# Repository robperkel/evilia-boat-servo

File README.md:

# Dr. Evilia's Boat Sampling HAT
This custom HAT is used to better implement control of the servos and motors used on her sampling boat. We found there wasn't a good "off-the-shelf" board available that fit the desired specifications. This project is designed around a small, 8-bit microcontroller that provides a far more intelligent and flexible design interface. 

This repository contains the documentation, hardware files, and firmware used for this project. The boat runs on a Raspberry Pi 4, Model B.  

## Table of Contents

- [Base Software](#base-software)
- [Tools Needed](#tools-needed)
    - [Other Tools Used](#other-tools-used)
- [Bill of Materials (BOM)](#bill-of-materials-bom)
- [Design Objectives](#design-objectives)
- [Microcontroller Pinout](#microcontroller-pinout)
- [Software Registers](#software-registers)
- [Digital Control](#digital-control)
- [Analog Control](#analog-control)
- [Usage from Raspberry Pi](#usage-from-raspberry-pi)

## Base Software

This bare metal I<sup>2</sup>C driver was used as a code base: https://github.com/microchip-pic-avr-examples/pic18f56q71-bare-metal-i2c-mplab 

**Per the license agreement in this code, the firmware (specifically the I<sup>2</sup>C driver) can ONLY be used with Microchip microcontrollers.** This is not an issue as the physical board is not compatiable with other microcontrollers.

## Tools Needed

- Programming / Development IDE: [MPLAB&reg; X IDE v6.10](https://www.microchip.com/en-us/tools-resources/develop/mplab-x-ide)
- Compiler: [MPLAB XC8 v2.41](https://www.microchip.com/en-us/tools-resources/develop/mplab-xc-compilers/downloads-documentation#XC8)  
- Programmer: [MPLAB SNAP](https://www.microchip.com/en-us/development-tool/PG164100) or [PICKIT&trade; 4](https://www.microchip.com/en-us/development-tool/PG164140)

### Other Tools Used

- I<sup>2</sup>C Tester (for development): [MCP2221A Breakout Module (ADM00559)](https://www.microchip.com/en-us/development-tool/ADM00559)
- Block Diagrams: [Draw.io](https://app.diagrams.net/)
- Schematic and PCB Generation: [KiCad 7](https://www.kicad.org/)
- PCB Vendor: [OSH Park](https://oshpark.com/)
    - If ordering from a different vendor, I recommend choosing a surface finish such as ENIG to provide some corrosion resistance in the high humidity environment.
    - Conformally coating the board is also recommended.

## Bill of Materials (BOM)

Order PCBs directly from the [OSH Park Project Page](https://oshpark.com/shared_projects/IClJSFr6)  
Digikey Shopping List: [https://www.digikey.com/en/mylists/list/YOLHZE0EBO](https://www.digikey.com/en/mylists/list/YOLHZE0EBO)   
- See [Control Board.xlsx](./Control%20Board/Control%20Board.xlsx) for the BOM
    - Red, struck-through items are not in the BOM
- Includes 0 ohm jumpers for I<sup>2</sup>C Address Setting
- Motor drive parts for `EXT_LED1` are not included
- Optional off-board connectors are not in the list

**Important: Shopping list does NOT include a programmer. Programmers can obtained from Digikey (or other electronics vendor).**

## Design Objectives

1. Support 6x 3-pin servo motors
2. ON/OFF control of a large pump
3. LED outputs for various indicators
4. I<sup>2</sup>C Interface
5. 3.3V logic interface with Raspberry Pi
6. 5V, 500mA motor control (ON/OFF)
7. 50 Hz Servo Frequency

## Microcontroller Pinout

Microcontroller: PIC18F1xQ41
(PIC18F14Q41 / PIC18F15Q41 / PIC18F16Q41)

| Function | Pin (PORT / PIN)
| -------- | ----------
| VDD (5V) | 1
| VSS (GND) | 20
| nMCLR | 4
| SDA | 2 (RA5)
| SCL | 3 (RA4)
| ADDR0 | 16 (RC0)
| ADDR1 | 13 (RB4)
| Servo 6 | 10 (RB7)
| Servo 5 | 9 (RC7)
| Servo 4 | 8 (RC6)
| Servo 3 | 7 (RC3)
| Servo 2 | 6 (RC4)
| Servo 1 | 5 (RC5)
| EXT_LED | 11 (RB6)
| PUMP_EN | 15 (RC1)
| AN1 | 17 (RA2)
| AN2 | 12 (RB5)
| DEBUG 0 | 19 (RA0 / ICSPDAT)
| DEBUG 1 | 18 (RA1 / ICSPCLK)
| OPAMP_OUT (reserved) | 14 (RC2)

### Notes
1. nMCLR is not available as an I/O in this configuration.
2. DEBUG 0/1 are LED outputs on the board. Unavailable during debugging.
3. EXT_LED can be converted to a 2nd motor/pump enable.
4. OPAMP_OUT is reserved due to internal OPAMP peripheral requirements.  

## Software Registers

**Please see [Registers.md](./Registers.md) for more information**

## Digital Control

### I<sup>2</sup>C Parameters

- Frequency: 100 kHz  
- 7-bit Address: TBD

### I<sup>2</sup>C Communication

### Writing To

The "register address" (Reg. ADDR) selects which setting to change. After this, each data byte is loaded into the next sequential register. 

(Start) &rarr; I<sup>2</sup>C ADDR (W) &rarr; Reg. ADDR &rarr; Data 0 &rarr; Data 1 &rarr; ... &rarr; Data N &rarr; (Stop)

### Reading From

To read from the device, address the microcontroller (write) and send the starting register address. Then, restart communication and address the microcontroller (read). Each byte is read in order from the registers.

(Start) &rarr; I<sup>2</sup>C ADDR (W) &rarr; Reg. ADDR &rarr; (Restart) &rarr; I<sup>2</sup>C ADDR (R) &rarr; Data 0 &rarr; Data 1 &rarr; ... &rarr; Data N &rarr; (Stop)

### Power on Restart (PoR) Behavior

On PoR, the microcontroller sets all duty cycles to 0%, PWM frequencies to 50 Hz, and turns off the LEDs and motor. 

## Analog Control

## Usage from Raspberry Pi

To ease integration in the system, a custom Python library was developed to simplify setup.

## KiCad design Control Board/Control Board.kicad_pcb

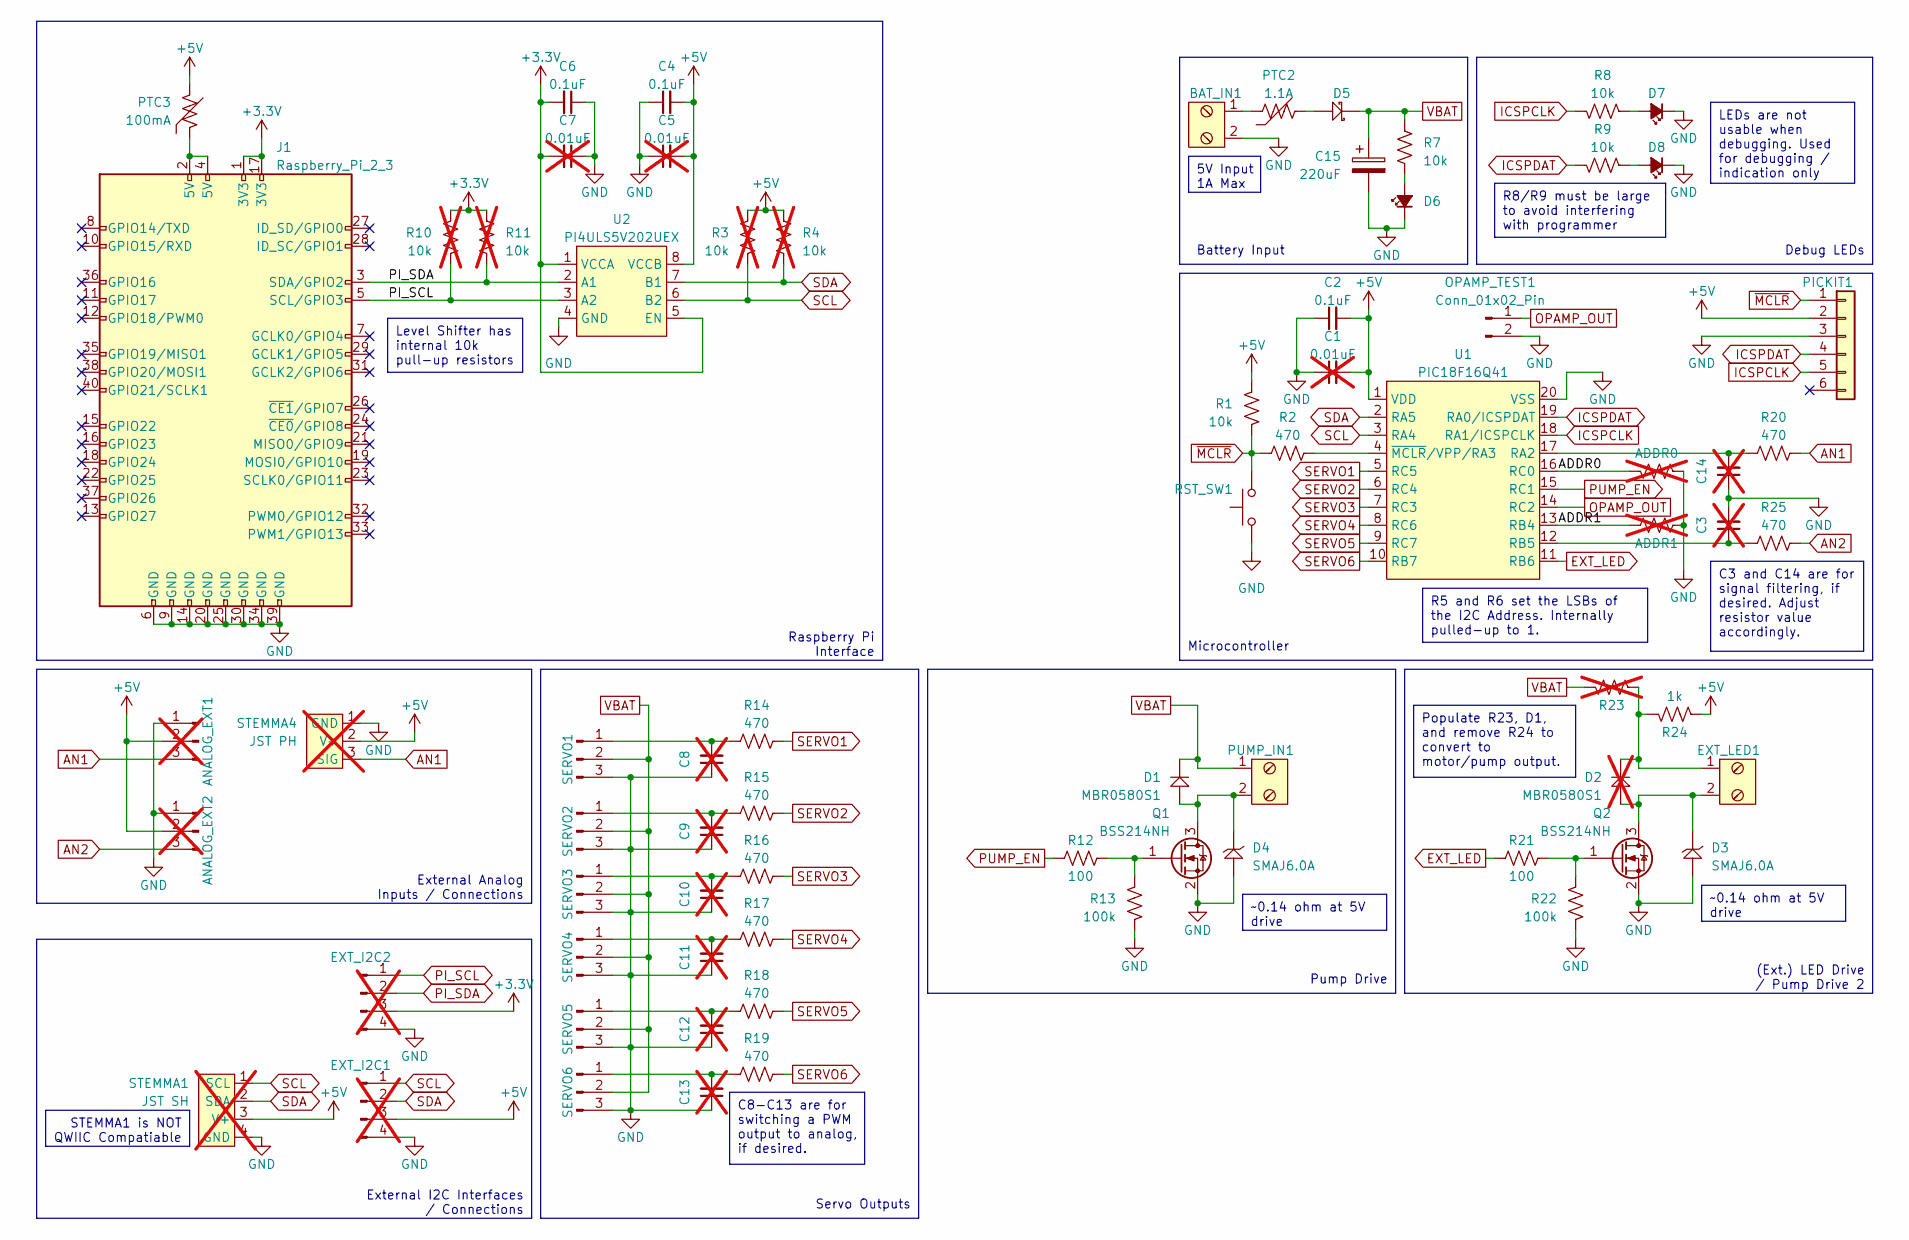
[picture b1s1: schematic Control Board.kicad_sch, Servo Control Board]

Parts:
ADDR0, ADDR1: 0; R_0805_2012Metric_Pad1.20x1.40mm_HandSolder; not fitted
ANALOG_EXT1, ANALOG_EXT2: Conn_01x03_Pin; PinHeader_1x03_P2.54mm_Vertical; not fitted
BAT_IN1: BCH-381H-2 GN; BCH-381H-2GN
C1, C3, C5, C7, C8, C9, C10, C11, C12, C13, C14: 0.01uF; C_0805_2012Metric_Pad1.18x1.45mm_HandSolder; not fitted
C2, C4, C6: 0.1uF; C_0805_2012Metric_Pad1.18x1.45mm_HandSolder
C15: 220uF; C_Radial_D8.0mm_H11.5mm_P3.50mm
D1: MBR0580S1; SOD-123
D2: MBR0580S1; SOD-123; not fitted
D3, D4: SMAJ6.0A; DO-214AC
D5: B240AE-13; DO-214AC
D6, D7, D8: LED_Small_Filled; LED_0805_2012Metric_Pad1.15x1.40mm_HandSolder
EXT_I2C1, EXT_I2C2: Conn_01x04_Pin; PinHeader_1x04_P2.54mm_Vertical; not fitted
EXT_LED1: BCH-381H-2 GN; BCH-381H-2GN
J1: Raspberry_Pi_2_3; PinHeader_2x20_P2.54mm_Vertical
OPAMP_TEST1: Conn_01x02_Pin; PinHeader_1x02_P2.54mm_Vertical
PICKIT1: Conn_01x06; PinHeader_1x06_P2.54mm_Horizontal
PTC2: 1.1A; 0ZCG Series PTC
PTC3: 100mA; 0ZCG Series PTC
PUMP_IN1: BCH-381H-2 GN; BCH-381H-2GN
Q1, Q2: BSS214NH; SOT23-3
R1, R7, R8, R9: 10k; R_0805_2012Metric_Pad1.20x1.40mm_HandSolder
R2, R14, R15, R16, R17, R18, R19, R20, R25: 470; R_0805_2012Metric_Pad1.20x1.40mm_HandSolder
R3, R4, R10, R11: 10k; R_0805_2012Metric_Pad1.20x1.40mm_HandSolder; not fitted
R12, R21: 100; R_0805_2012Metric_Pad1.20x1.40mm_HandSolder
R13, R22: 100k; R_0805_2012Metric_Pad1.20x1.40mm_HandSolder
R23: 0; R_0805_2012Metric_Pad1.20x1.40mm_HandSolder; not fitted
R24: 1k; R_0805_2012Metric_Pad1.20x1.40mm_HandSolder
RST_SW1: TL6400AF160QJ
SERVO1, SERVO2, SERVO3, SERVO4, SERVO5, SERVO6: Conn_01x03_Pin; PinHeader_1x03_P2.54mm_Vertical
STEMMA1: JST SH; Adafruit STEMMA, 4-pin JST SH; not fitted
STEMMA4: JST PH; Adafruit STEMMA, 3-pin JST PH; not fitted
U1: PIC18F16Q41; SSOP-20, 5.3mm Body
U2: PI4ULS5V202UEX; MSOP-8

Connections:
+3.3V: C6.2, C7.2, EXT_I2C2.3, J1.1 (3V3), J1.17 (3V3), R10.1, R11.1, U2.1 (VCCA), U2.5 (EN)
+5V: ANALOG_EXT1.2, ANALOG_EXT2.2, C1.2, C2.2, C4.2, C5.2, EXT_I2C1.3, PICKIT1.2, PTC3.2, R1.1, R3.1, R4.1, R24.2, STEMMA1.3 (V+), STEMMA4.2 (V+), U1.1 (VDD), U2.8 (VCCB)
/ADDR0: ADDR0.1, U1.16 (RC0)
/ADDR1: ADDR1.1, U1.13 (RB4)
AN1: ANALOG_EXT1.3, R20.2, STEMMA4.3 (SIG)
AN2: ANALOG_EXT2.3, R25.2
EXT_LED: R21.1, U1.11 (RB6)
GND: ADDR0.2, ADDR1.2, ANALOG_EXT1.1, ANALOG_EXT2.1, BAT_IN1.2, C1.1, C2.1, C3.2, C4.1, C5.1, C6.1, C7.1, C8.1, C9.1, C10.1, C11.1, C12.1, C13.1, C14.1, C15.2, D3.A, D4.A, D6.1 (K), D7.1 (K), D8.1 (K), EXT_I2C1.4, EXT_I2C2.4, J1.6 (GND), J1.9 (GND), J1.14 (GND), J1.20 (GND), J1.25 (GND), J1.30 (GND), J1.34 (GND), J1.39 (GND), OPAMP_TEST1.2, PICKIT1.3, Q1.2 (S), Q2.2 (S), R13.2, R22.2, RST_SW1.1, SERVO1.3, SERVO2.3, SERVO3.3, SERVO4.3, SERVO5.3, SERVO6.3, STEMMA1.4 (GND), STEMMA4.1 (GND), U1.20 (VSS), U2.4 (GND)
ICSPCLK: PICKIT1.5, R8.2, U1.18 (RA1/ICSPCLK)
ICSPDAT: PICKIT1.4, R9.2, U1.19 (RA0/ICSPDAT)
unnamed: BAT_IN1.1, PTC2.1
unnamed: D2.K, EXT_LED1.1, R23.2, R24.1
unnamed: D5.A, PTC2.2
unnamed: D6.2 (A), R7.2
unnamed: D7.2 (A), R8.1
unnamed: D8.2 (A), R9.1
unnamed: J1.2 (5V), J1.4 (5V), PTC3.1
unnamed: D1.A, D4.K, PUMP_IN1.2, Q1.3 (D)
unnamed: Q1.1 (G), R12.2, R13.1
unnamed: D2.A, D3.K, EXT_LED1.2, Q2.3 (D)
unnamed: Q2.1 (G), R21.2, R22.1
unnamed: C8.2, R14.1, SERVO1.1
unnamed: C9.2, R15.1, SERVO2.1
unnamed: C10.2, R16.1, SERVO3.1
unnamed: C11.2, R17.1, SERVO4.1
unnamed: C12.2, R18.1, SERVO5.1
unnamed: C13.2, R19.1, SERVO6.1
unnamed: C14.2, R20.1, U1.17 (RA2)
unnamed: C3.1, R25.1, U1.12 (RB5)
unnamed: R2.2, U1.4 (~MCLR/VPP/RA3)
OPAMP_OUT: OPAMP_TEST1.1, U1.14 (RC2)
PI_SCL: EXT_I2C2.1, J1.5 (SCL/GPIO3), R10.2, U2.3 (A2)
PI_SDA: EXT_I2C2.2, J1.3 (SDA/GPIO2), R11.2, U2.2 (A1)
PUMP_EN: R12.1, U1.15 (RC1)
SCL: EXT_I2C1.1, R3.2, STEMMA1.1 (SCL), U1.3 (RA4), U2.6 (B2)
SDA: EXT_I2C1.2, R4.2, STEMMA1.2 (SDA), U1.2 (RA5), U2.7 (B1)
SERVO1: R14.2, U1.5 (RC5)
SERVO2: R15.2, U1.6 (RC4)
SERVO3: R16.2, U1.7 (RC3)
SERVO4: R17.2, U1.8 (RC6)
SERVO5: R18.2, U1.9 (RC7)
SERVO6: R19.2, U1.10 (RB7)
VBAT: C15.1, D1.K, D5.K, PUMP_IN1.1, R7.1, R23.1, SERVO1.2, SERVO2.2, SERVO3.2, SERVO4.2, SERVO5.2, SERVO6.2
~MCLR: PICKIT1.1, R1.2, R2.1, RST_SW1.2

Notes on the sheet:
Populate R23, D1, and remove R24 to convert to motor/pump output.
Debug LEDs
External Analog Inputs / Connections
Battery Input
~0.14 ohm at 5V drive
R8/R9 must be large to avoid interfering with programmer
5V Input 1A Max
C3 and C14 are for signal filtering, if desired. Adjust resistor value accordingly.
C8-C13 are for switching a PWM output to analog, if desired.
External I2C Interfaces / Connections
LEDs are not usable when debugging. Used for debugging / indication only
Pump Drive
Level Shifter has internal 10k pull-up resistors
R5 and R6 set the LSBs of the I2C Address. Internally pulled-up to 1.
Servo Outputs
Microcontroller
(Ext.) LED Drive / Pump Drive 2
STEMMA1 is NOT QWIIC Compatiable
Raspberry Pi Interface

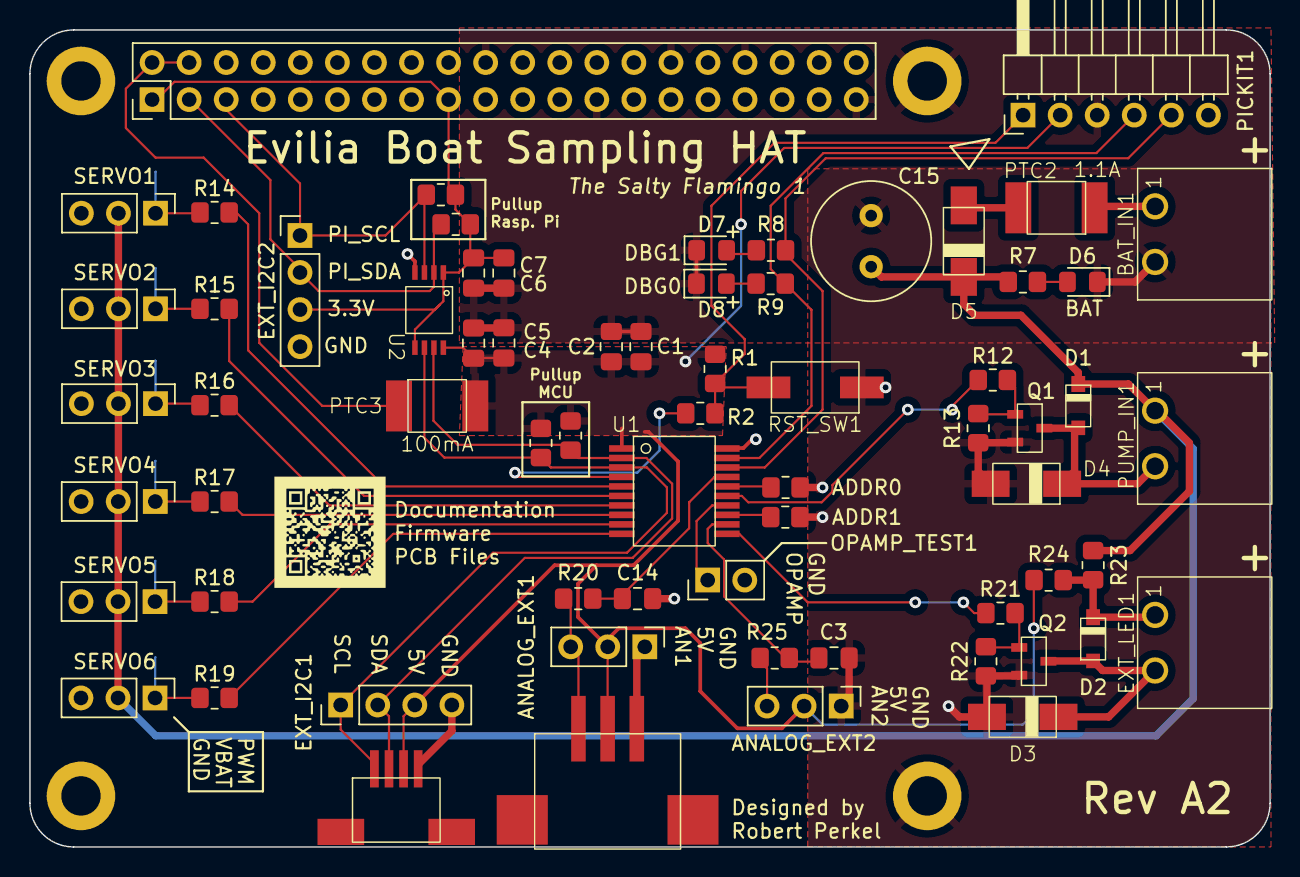
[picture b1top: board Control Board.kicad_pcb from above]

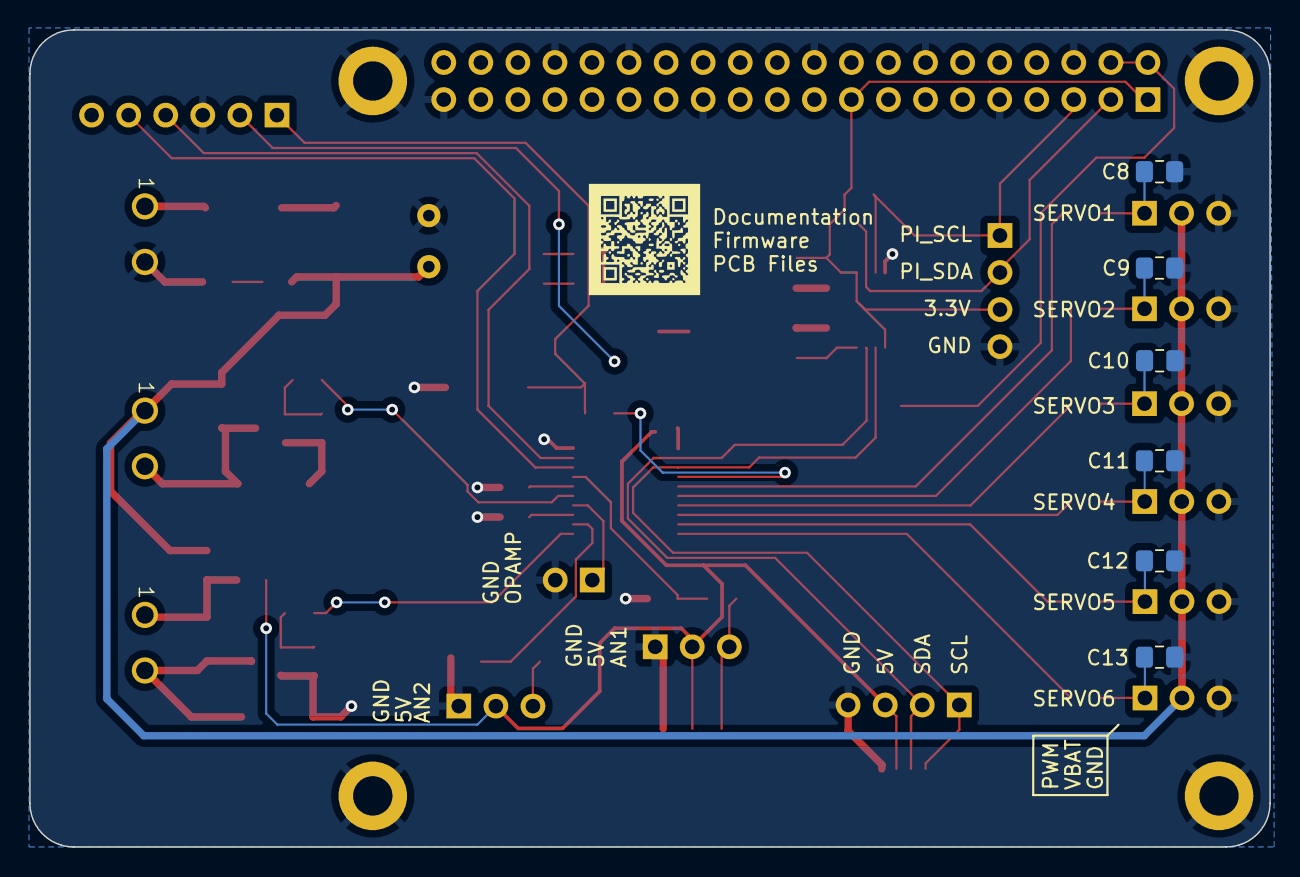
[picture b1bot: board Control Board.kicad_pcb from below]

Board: 2 copper layers, 85.0 x 56.0 mm, 73 parts (6 on the bottom side), 44 nets.

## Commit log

2023-06-01 Update README.md
    Added basic documentation
2023-06-14 Improvements to schematic
2023-06-16 Work on Schematic + README
2023-06-19 Started PCB layout
2023-06-27 More changes to PCB / Schematic
    Schematic complete, PCB in progress
2023-06-29 More work on PCB
2023-06-29 Draft of PCB
2023-06-29 Finished PCB
2023-07-01 Started Firmware Image
2023-07-03 README changes and block diagram
2023-07-07 Firmware Tweaks, Schematic Notations
    Began to implement SW Registers. Adjusted part annotations / DNP status (no layout changes)
2023-07-09 Started to implement other HAL files
2023-07-10 PWM / NCO Code
2023-07-11 More work on APIs
2023-07-11 Moved register specification to separate file
2023-07-12 GPIO HAL Improvements
2023-07-14 Work on HAL
2023-07-15 Firmware tweaks
    Began to test firmware on physical hardware.
2023-07-15 More work on firmware
2023-07-17 Analog HAL. Adjusted registers
2023-07-17 Added more functions to analog HAL
2023-07-18 Bug fixes. Added VSS input
2023-07-18 Bug fixes. Added test script for MCP2221A
2023-07-18 Improved I2C Error Handling
2023-07-21 Added DAC2 for Self-Testing. Updated PCB/SCH to Rev A2
    Increased size of pads for reset switch. Added debug header for OPAMP. Added pin 1 marker for programming.
2023-07-21 PCB fixes
2023-07-25 Initial Commit of Python Library
    Includes bug fix for Pump
2023-07-29 Updated python scripts to newest versions. Added debouncing
2024-03-21 Changed default PWM DC
2025-05-19 Added 3d models
